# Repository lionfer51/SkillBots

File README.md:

# SkillBots
Repositorio oficial de SkillBots (RAS-UNFV)

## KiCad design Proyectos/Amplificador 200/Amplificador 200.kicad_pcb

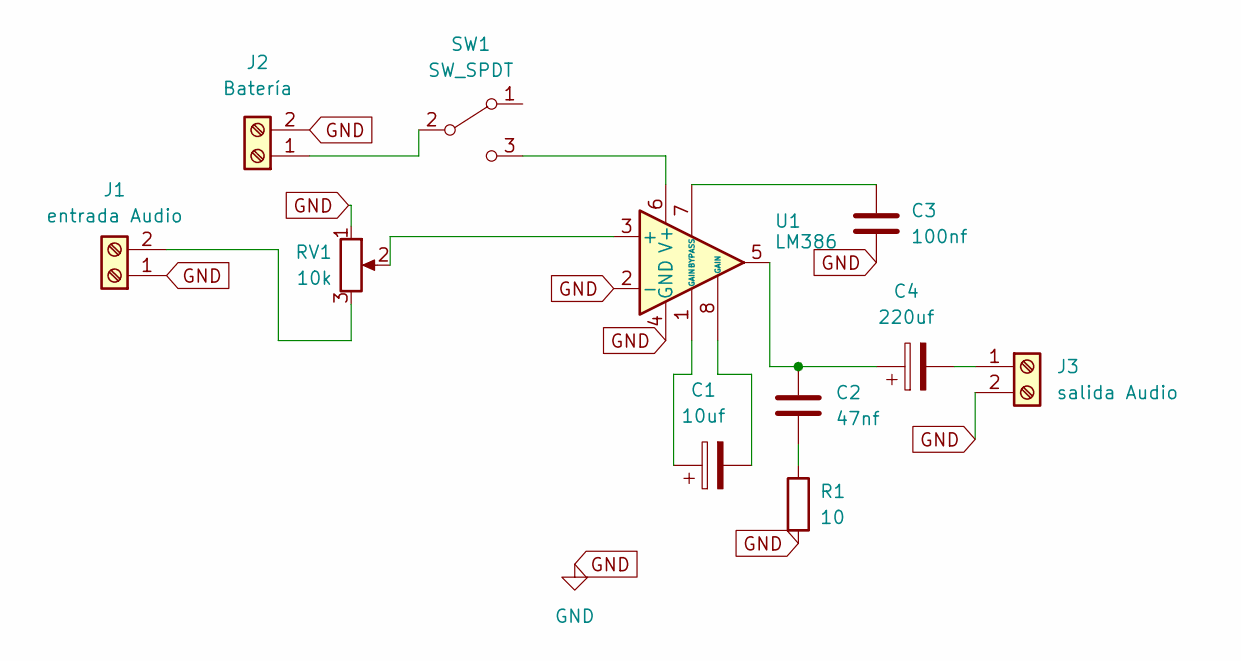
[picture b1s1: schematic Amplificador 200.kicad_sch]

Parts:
C1: 10uf; CP_Radial_D5.0mm_P2.50mm
C2: 47nf; C_Disc_D3.0mm_W2.0mm_P2.50mm
C3: 100nf; C_Disc_D3.0mm_W2.0mm_P2.50mm
C4: 220uf; CP_Radial_D5.0mm_P2.50mm
J1: entrada Audio; TerminalBlock_bornier-2_P5.08mm
J2: Batería; TerminalBlock_bornier-2_P5.08mm
J3: salida Audio; TerminalBlock_bornier-2_P5.08mm
R1: 10; R_Axial_DIN0204_L3.6mm_D1.6mm_P5.08mm_Horizontal
RV1: 10k; Potentiometer_Piher_T-16H_Single_Horizontal
SW1: SW_SPDT; SW_MINI-SPDT-SW
U1: LM386; DIP08

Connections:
GND: C3.2, J1.1, J2.2, J3.2, R1.2, RV1.1, U1.2 (-), U1.4 (GND)
unnamed: C1.1, U1.1 (GAIN)
unnamed: C1.2, U1.8 (GAIN)
unnamed: C2.1, C4.1, U1.5
unnamed: C2.2, R1.1
unnamed: J1.2, RV1.3
unnamed: J2.1, SW1.2 (B)
unnamed: C4.2, J3.1
unnamed: SW1.3 (C), U1.6 (V+)
unnamed: RV1.2, U1.3 (+)
unnamed: C3.1, U1.7 (BYPASS)

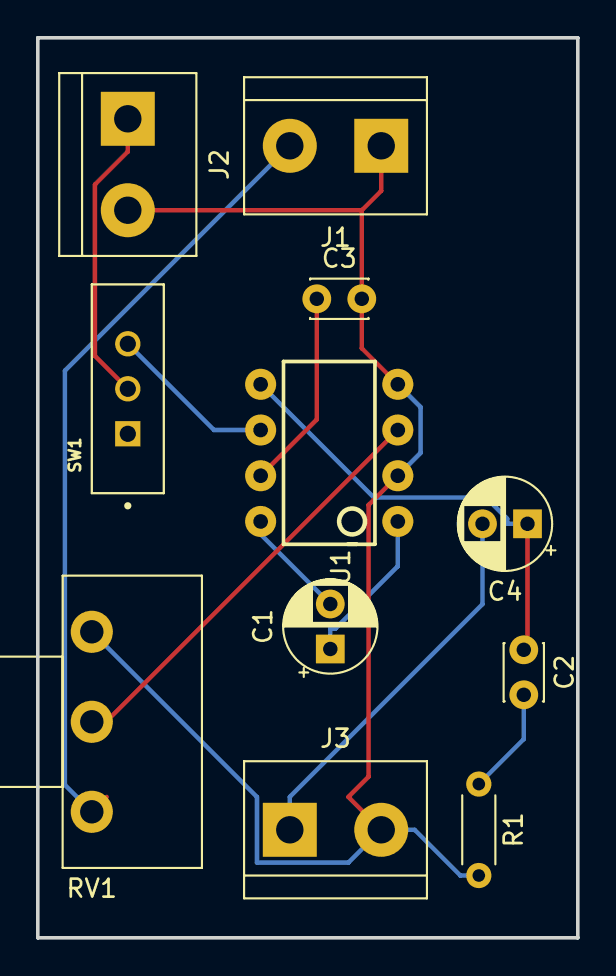
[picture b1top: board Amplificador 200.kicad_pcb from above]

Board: 2 copper layers, 30.0 x 50.0 mm, 11 parts (0 on the bottom side), 11 nets.

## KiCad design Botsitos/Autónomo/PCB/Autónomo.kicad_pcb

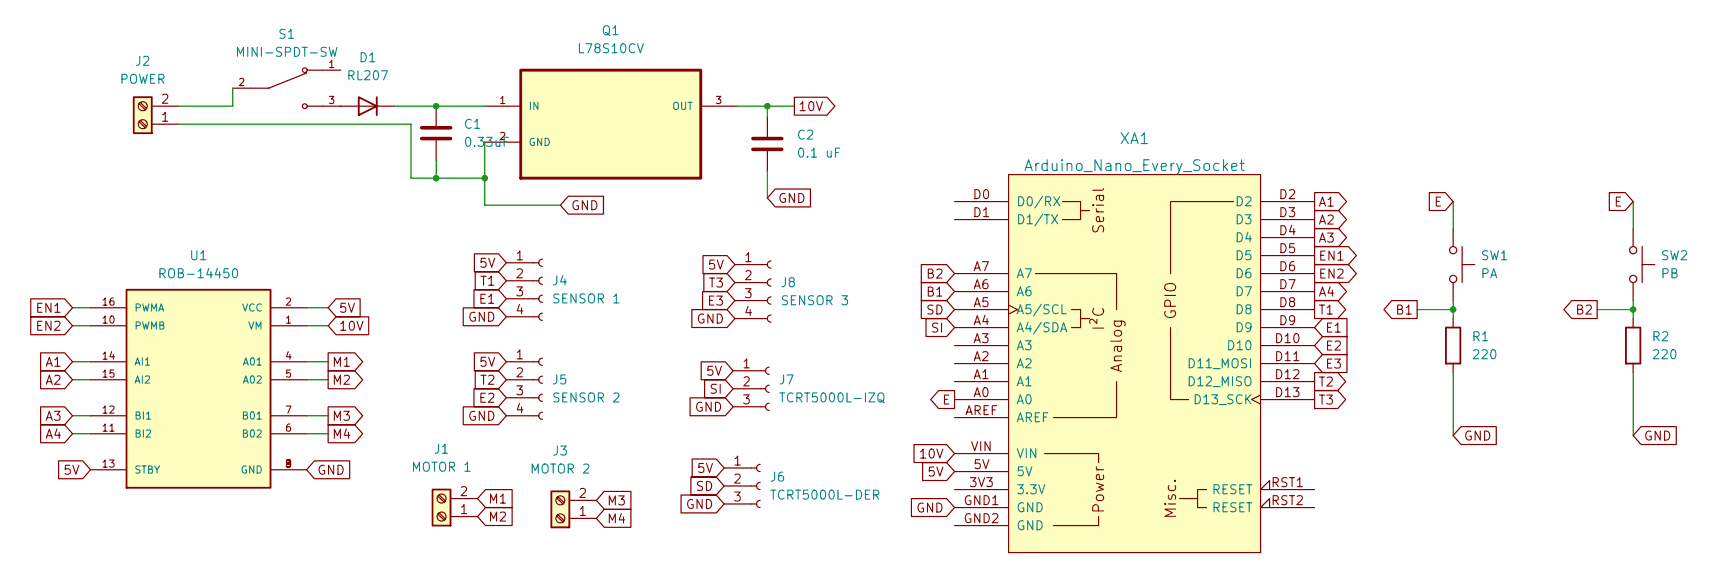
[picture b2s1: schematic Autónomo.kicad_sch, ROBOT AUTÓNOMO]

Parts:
C1: 0.33uF; C_Disc_D3.8mm_W2.6mm_P2.50mm
C2: 0.1 uF; C_Disc_D3.8mm_W2.6mm_P2.50mm
D1: RL207; D_DO-41_SOD81_P10.16mm_Horizontal
J1: MOTOR 1; TerminalBlock_bornier-2_P5.08mm
J2: POWER; TerminalBlock_bornier-2_P5.08mm
J3: MOTOR 2; TerminalBlock_bornier-2_P5.08mm
J4: SENSOR 1; PinSocket_1x04_P2.54mm_Vertical
J5: SENSOR 2; PinSocket_1x04_P2.54mm_Vertical
J6: TCRT5000L-DER; PinSocket_1x03_P2.54mm_Vertical
J7: TCRT5000L-IZQ; PinSocket_1x03_P2.54mm_Vertical
J8: SENSOR 3; PinSocket_1x04_P2.54mm_Vertical
Q1: L78S10CV; TO254P450X1020X1935-3P; MPN L78S10CV
R1, R2: 220; R_Axial_DIN0204_L3.6mm_D1.6mm_P5.08mm_Horizontal
S1: MINI-SPDT-SW; SW_MINI-SPDT-SW; PARTREV C
SW1: PA; SW_PUSH_6mm_H13mm
SW2: PB; SW_PUSH_6mm_H13mm
U1: ROB-14450; MODULE_ROB-14450; PARTREV 11-13-17
XA1: Arduino_Nano_Every_Socket

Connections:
5V: J4.1, J5.1, J6.1, J7.1, J8.1, U1.2 (VCC), U1.13 (STBY), XA1.5V
10V: C2.1, Q1.3 (OUT), U1.1 (VM), XA1.VIN
A1: U1.14 (AI1), XA1.D2
A2: U1.15 (AI2), XA1.D3
A3: U1.12 (BI1), XA1.D4
A4: U1.11 (BI2), XA1.D7
B1: R1.1, SW1.2, XA1.A6
B2: R2.1, SW2.2, XA1.A7
E: SW1.1, SW2.1, XA1.A0
E1: J4.3, XA1.D9
E2: J5.3, XA1.D10
E3: J8.3, XA1.D11 (D11_MOSI)
EN1: U1.16 (PWMA), XA1.D5
EN2: U1.10 (PWMB), XA1.D6
GND: C1.1, C2.2, J2.1, J4.4, J5.4, J6.3, J7.3, J8.4, Q1.2 (GND), R1.2, R2.2, U1.3 (GND), U1.8 (GND), U1.9 (GND), XA1.GND1 (GND)
M1: J1.2, U1.4 (A01)
M2: J1.1, U1.5 (A02)
M3: J3.2, U1.7 (B01)
M4: J3.1, U1.6 (B02)
unnamed: C1.2, D1.1 (K), Q1.1 (IN)
unnamed: D1.2 (A), S1.3
unnamed: J2.2, S1.2
SD: J6.2, XA1.A5 (A5/SCL)
SI: J7.2, XA1.A4 (A4/SDA)
T1: J4.2, XA1.D8
T2: J5.2, XA1.D12 (D12_MISO)
T3: J8.2, XA1.D13 (D13_SCK)

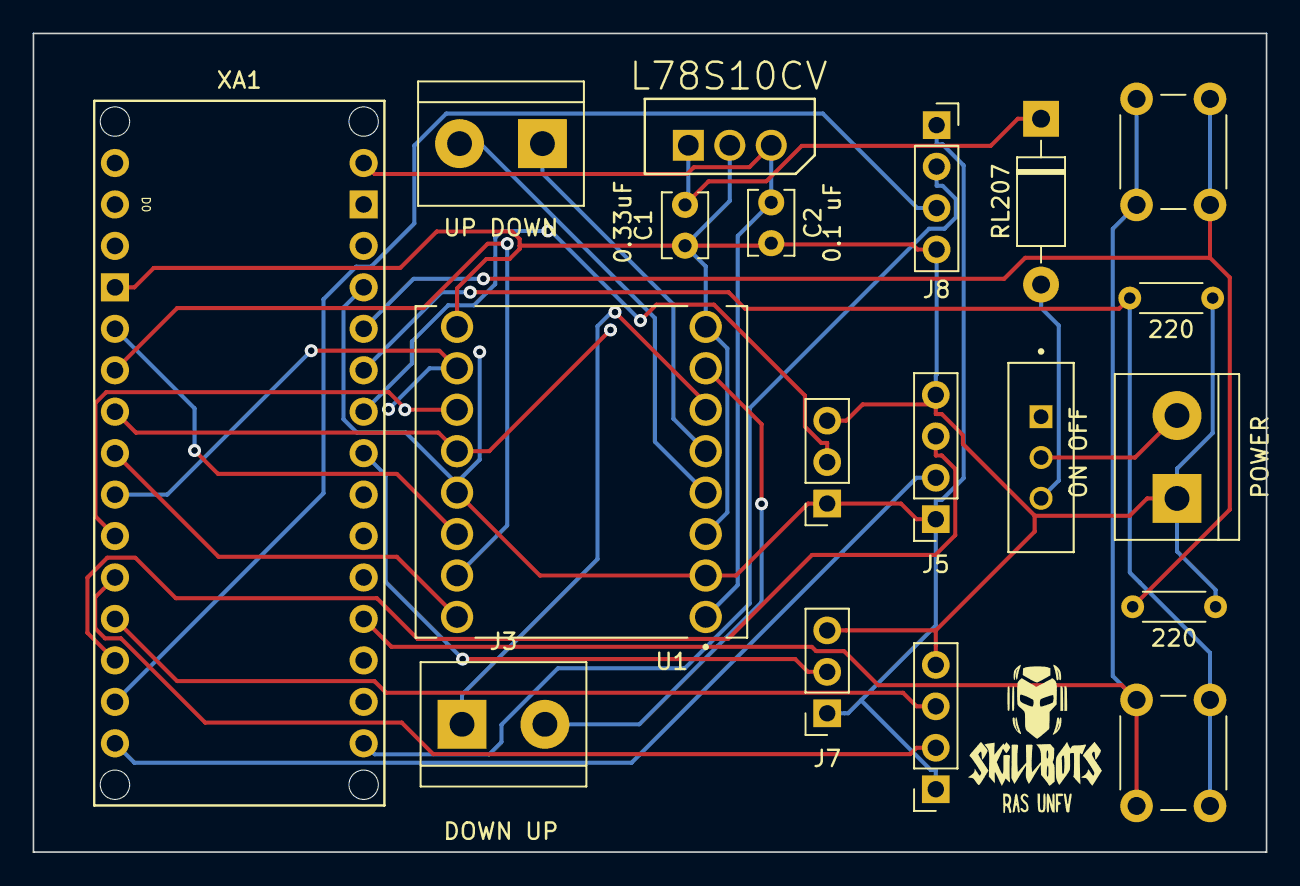
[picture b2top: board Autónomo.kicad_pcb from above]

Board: 2 copper layers, 75.6 x 50.2 mm, 19 parts (0 on the bottom side), 27 nets.

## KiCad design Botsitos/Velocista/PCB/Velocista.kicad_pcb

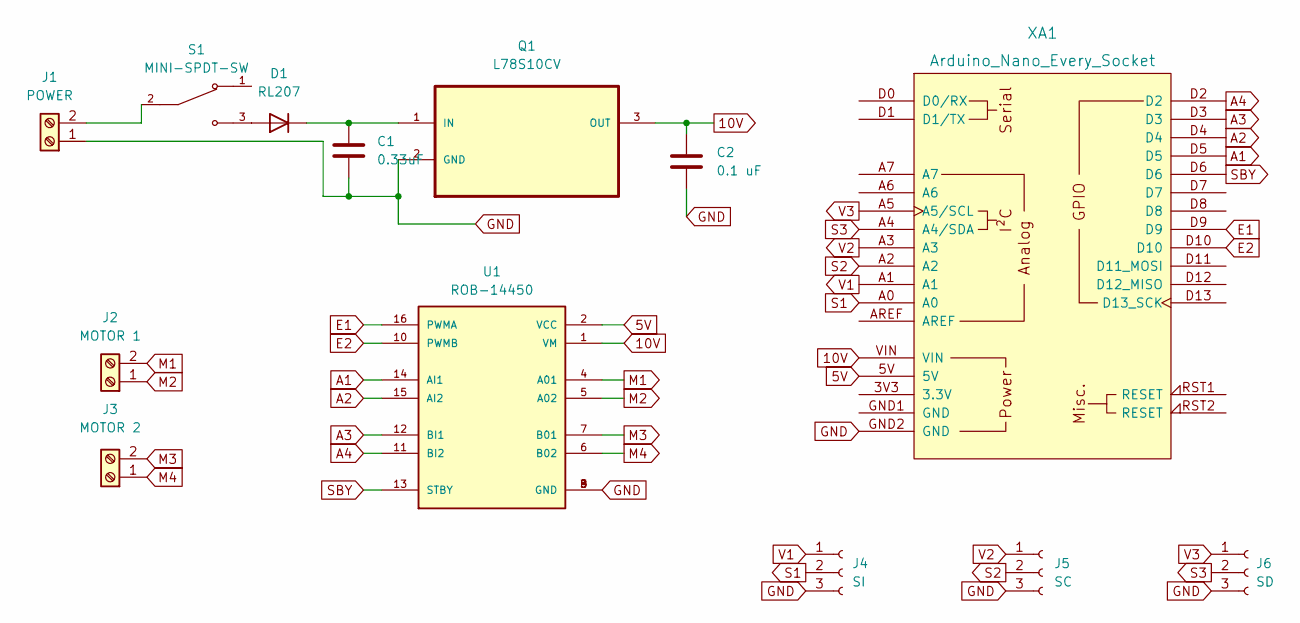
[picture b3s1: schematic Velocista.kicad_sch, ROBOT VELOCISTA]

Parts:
C1: 0.33uF; C_Disc_D3.8mm_W2.6mm_P2.50mm
C2: 0.1 uF; C_Disc_D3.8mm_W2.6mm_P2.50mm
D1: RL207; D_DO-41_SOD81_P10.16mm_Horizontal
J1: POWER; TerminalBlock_bornier-2_P5.08mm
J2: MOTOR 1; TerminalBlock_Phoenix_MPT-0,5-2-2.54_1x02_P2.54mm_Horizontal
J3: MOTOR 2; TerminalBlock_Phoenix_MPT-0,5-2-2.54_1x02_P2.54mm_Horizontal
J4: SI; PinSocket_1x03_P2.54mm_Vertical
J5: SC; PinSocket_1x03_P2.54mm_Vertical
J6: SD; PinSocket_1x03_P2.54mm_Vertical
Q1: L78S10CV; TO254P450X1020X1935-3P; MPN L78S10CV
S1: MINI-SPDT-SW; SW_MINI-SPDT-SW; PARTREV C
U1: ROB-14450; MODULE_ROB-14450; PARTREV 11-13-17
XA1: Arduino_Nano_Every_Socket

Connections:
5V: U1.2 (VCC), XA1.5V
10V: C2.1, Q1.3 (OUT), U1.1 (VM), XA1.VIN
A1: U1.14 (AI1), XA1.D5
A2: U1.15 (AI2), XA1.D4
A3: U1.12 (BI1), XA1.D3
A4: U1.11 (BI2), XA1.D2
E1: U1.16 (PWMA), XA1.D9
E2: U1.10 (PWMB), XA1.D10
GND: C1.1, C2.2, J1.1, J4.3, J5.3, J6.3, Q1.2 (GND), U1.3 (GND), U1.8 (GND), U1.9 (GND), XA1.GND2 (GND)
M1: J2.2, U1.4 (A01)
M2: J2.1, U1.5 (A02)
M3: J3.2, U1.7 (B01)
M4: J3.1, U1.6 (B02)
unnamed: C1.2, D1.1 (K), Q1.1 (IN)
unnamed: D1.2 (A), S1.3
unnamed: J1.2, S1.2
S1: J4.2, XA1.A0
S2: J5.2, XA1.A2
S3: J6.2, XA1.A4 (A4/SDA)
SBY: U1.13 (STBY), XA1.D6
V1: J4.1, XA1.A1
V2: J5.1, XA1.A3
V3: J6.1, XA1.A5 (A5/SCL)

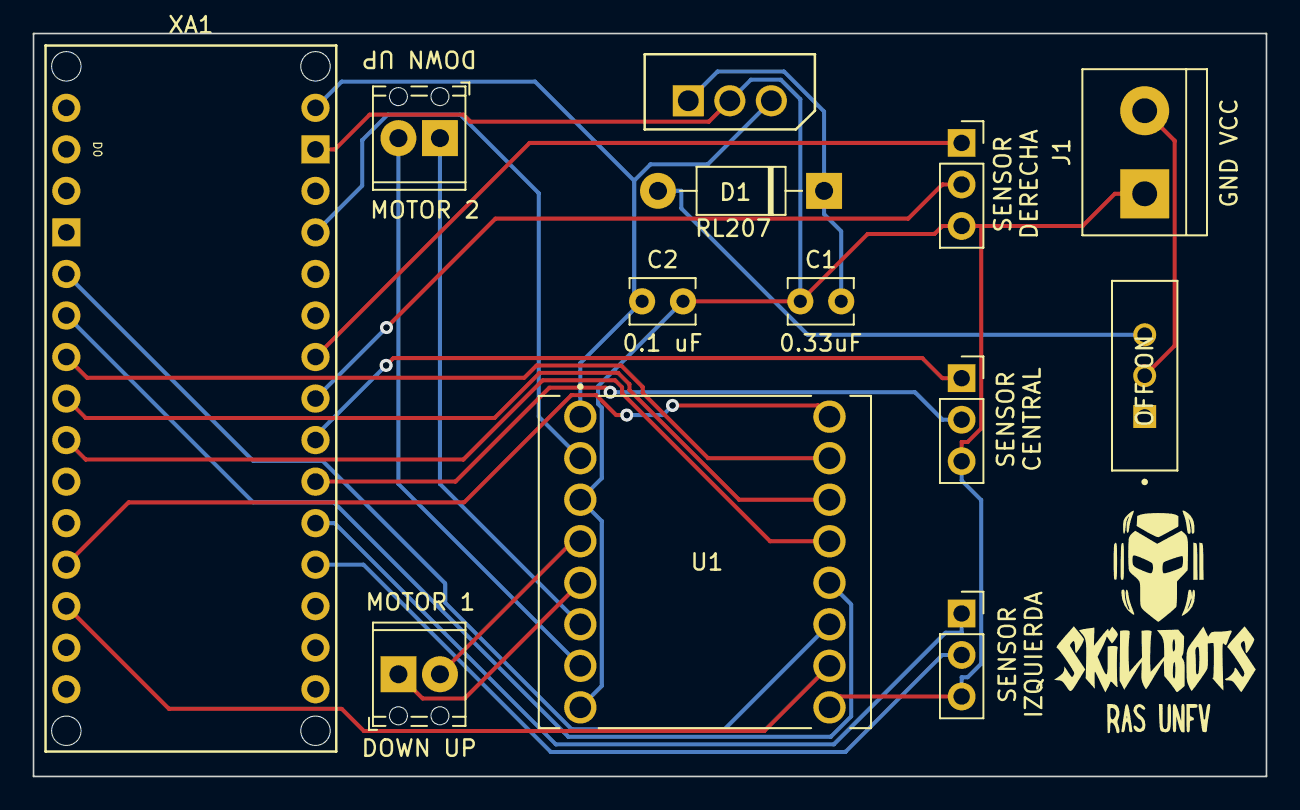
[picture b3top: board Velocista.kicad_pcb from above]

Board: 2 copper layers, 75.4 x 45.4 mm, 13 parts (0 on the bottom side), 23 nets.

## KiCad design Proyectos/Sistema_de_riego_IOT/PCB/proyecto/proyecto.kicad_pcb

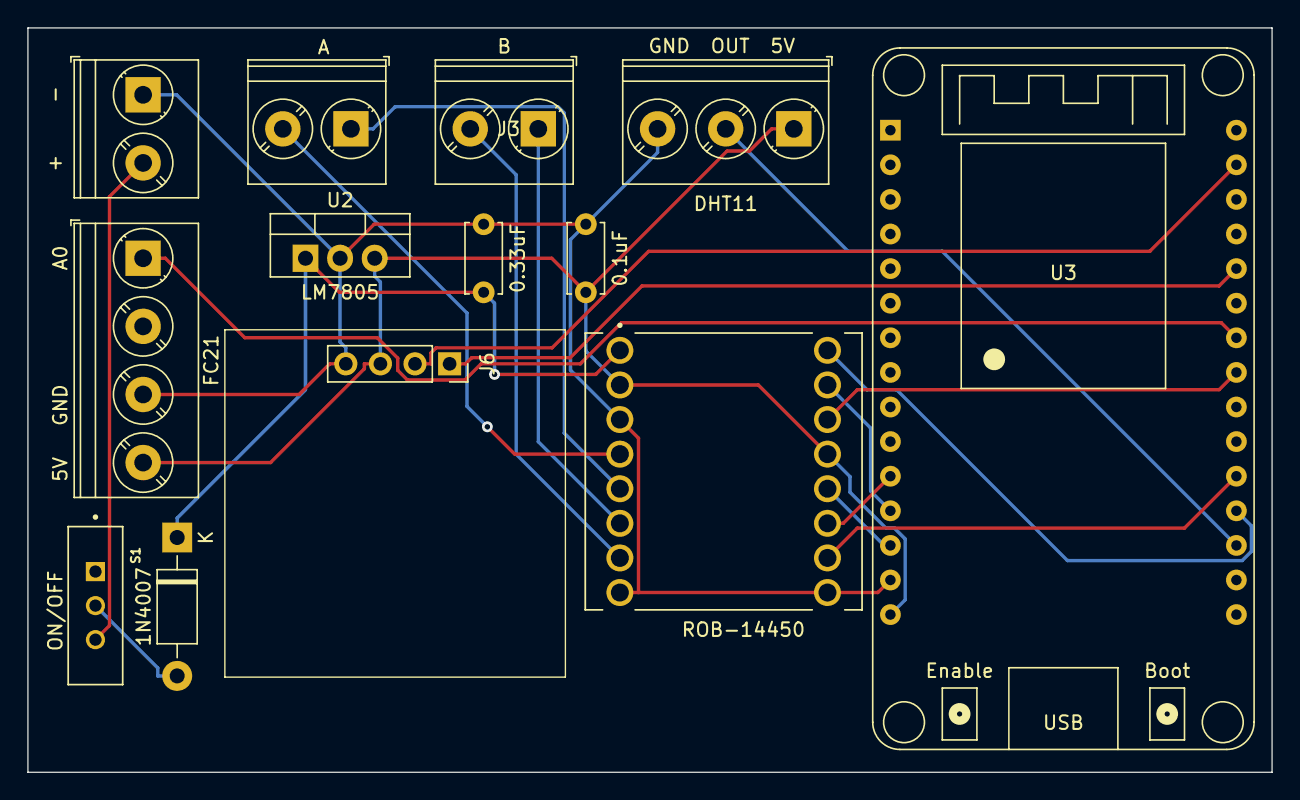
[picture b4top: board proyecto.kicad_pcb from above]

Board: 2 copper layers, 91.3 x 54.6 mm, 13 parts (0 on the bottom side), 19 nets.

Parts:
C1: 0.33uF; C_Disc_D5.0mm_W2.5mm_P5.00mm
C2: 0.1uF; C_Disc_D5.0mm_W2.5mm_P5.00mm
D1: 1N4007; D_DO-41_SOD81_P10.16mm_Horizontal
J1: + -; TerminalBlock_Phoenix_PT-1,5-2-5.0-H_1x02_P5.00mm_Horizontal
J2: DHT11; TerminalBlock_Phoenix_PT-1,5-3-5.0-H_1x03_P5.00mm_Horizontal
J3: B; TerminalBlock_Phoenix_PT-1,5-2-5.0-H_1x02_P5.00mm_Horizontal
J4: FC21; TerminalBlock_Phoenix_PT-1,5-4-5.0-H_1x04_P5.00mm_Horizontal
J5: A; TerminalBlock_Phoenix_PT-1,5-2-5.0-H_1x02_P5.00mm_Horizontal
J6: OLED; PinSocket_1x04_P2.54mm_Vertical
S1: ON/OFF; SW_MINI-SPDT-SW
U1: ROB-14450; MODULE_ROB-14450
U2: LM7805; TO-220-3_Vertical
U3: ESP32_DevKit_V1_DOIT; esp32_devkit_v1_doit

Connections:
5V: C2.1, J2.1, J4.4, J6.3, U1.2 (VCC), U1.13 (STBY), U2.3 (VO), U3.15 (VIN)
A0: J4.1, U3.24 (IO18)
GND: C1.2, C2.2, J1.1, J2.3, J4.3, J6.4, U1.3 (GND), U1.8 (GND), U1.9 (GND), U2.2 (GND), U3.14 (GND)
IA1: U1.14 (AI1), U3.23 (IO5)
IA2: U1.15 (AI2), U3.12 (IO12)
IB1: U1.12 (BI1), U3.13 (IO13)
IB2: U1.11 (BI2), U3.11 (IO14)
MA1: J5.2, U1.4 (A01)
MA2: J5.1, U1.5 (A02)
MB1: J3.2, U1.7 (B01)
MB2: J3.1, U1.6 (B02)
unnamed: D1.2 (A), S1.2
unnamed: J1.2, S1.3
OUT: J2.2, U3.18 (IO15)
PWMA: U1.16 (PWMA), U3.19 (IO2)
PWMB: U1.10 (PWMB), U3.20 (IO4)
SCL: J6.2, U3.29 (IO22)
SDA: J6.1, U3.26 (IO21)
V: C1.1, D1.1 (K), U1.1 (VM), U2.1 (VI)

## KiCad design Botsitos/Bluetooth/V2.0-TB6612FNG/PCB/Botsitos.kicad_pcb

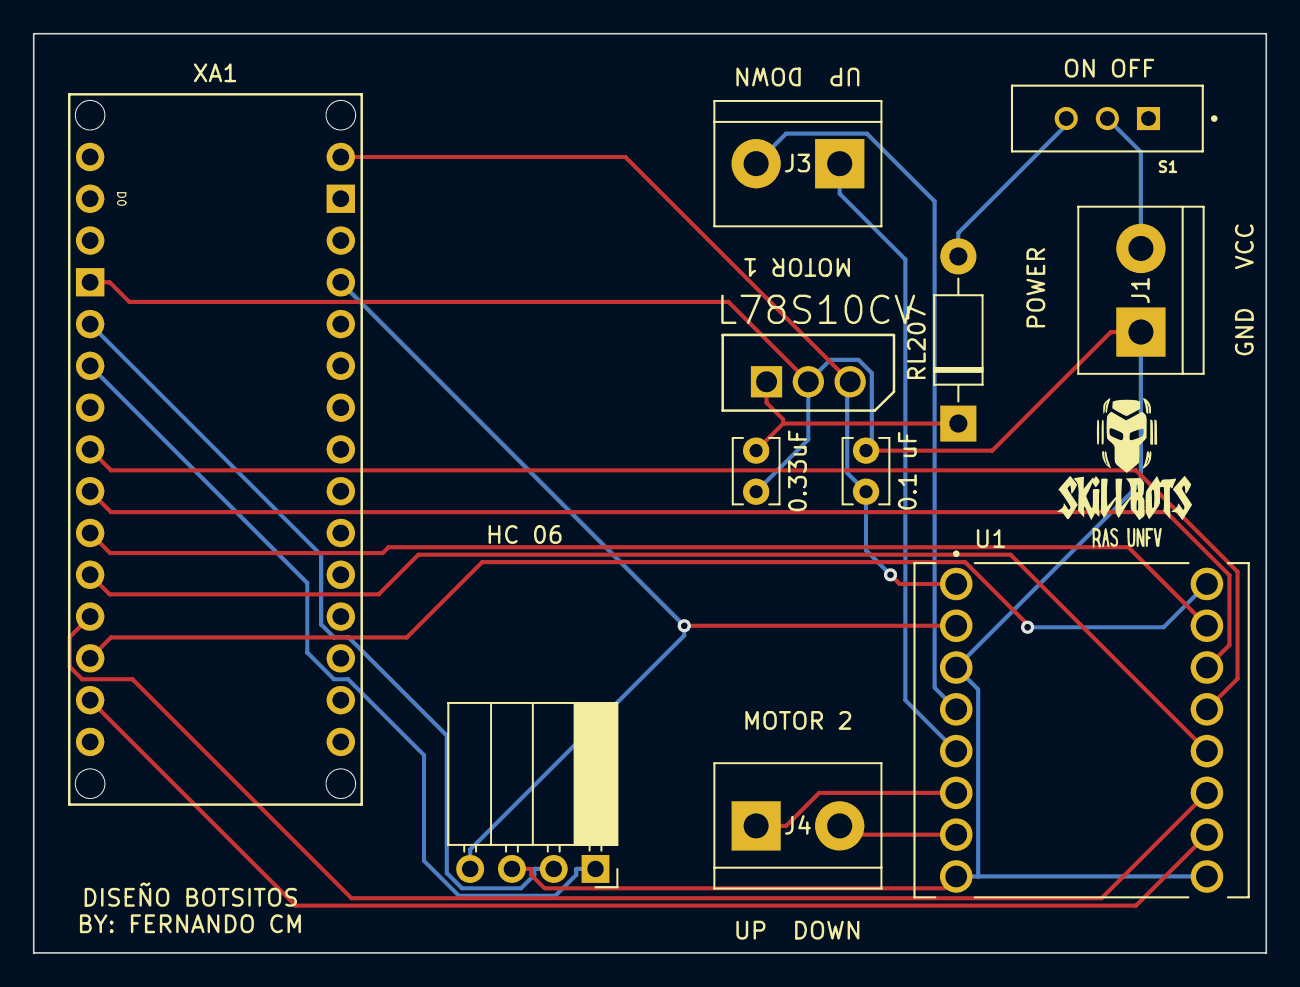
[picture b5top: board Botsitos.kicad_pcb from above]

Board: 2 copper layers, 74.9 x 55.9 mm, 11 parts (0 on the bottom side), 19 nets.

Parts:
C1: 0.33uF; C_Disc_D3.8mm_W2.6mm_P2.50mm
C2: 0.1 uF; C_Disc_D3.8mm_W2.6mm_P2.50mm
D1: RL207; D_DO-41_SOD81_P10.16mm_Horizontal
J1: POWER; TerminalBlock_bornier-2_P5.08mm
J2: HC06; PinSocket_1x04_P2.54mm_Horizontal
J3: MOTOR A; TerminalBlock_bornier-2_P5.08mm
J4: MOTOR B; TerminalBlock_bornier-2_P5.08mm
Q1: L78S10CV; TO254P450X1020X1935-3P
S1: MINI-SPDT-SW; SW_MINI-SPDT-SW
U1: ROB-14450; MODULE_ROB-14450
XA1: Arduino_Nano_Every_Socket

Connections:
5V: J2.4, U1.2 (VCC), XA1.5V
10V: C2.1, Q1.3 (OUT), U1.1 (VM), XA1.VIN
A1: U1.14 (AI1), XA1.D6
A2: U1.15 (AI2), XA1.D7
A3: U1.12 (BI1), XA1.D8
A4: U1.11 (BI2), XA1.D9
E1: U1.16 (PWMA), XA1.D10
E2: U1.10 (PWMB), XA1.D11 (D11_MOSI)
GND: C1.1, C2.2, J1.1, J2.3, Q1.2 (GND), U1.3 (GND), U1.8 (GND), U1.9 (GND), XA1.GND1 (GND)
M1: J3.2, U1.4 (A01)
M2: J3.1, U1.5 (A02)
M3: J4.2, U1.7 (B01)
M4: J4.1, U1.6 (B02)
unnamed: C1.2, D1.1 (K), Q1.1 (IN)
unnamed: D1.2 (A), S1.3
unnamed: J1.2, S1.2
RX: J2.1, XA1.D3
SBY: U1.13 (STBY), XA1.D5
TX: J2.2, XA1.D2

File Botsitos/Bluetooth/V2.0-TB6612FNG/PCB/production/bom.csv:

Designator,Footprint,Quantity,Value,LCSC Part #
C1,C_Disc_D3.8mm_W2.6mm_P2.50mm,1,0.33uF,
C2,C_Disc_D3.8mm_W2.6mm_P2.50mm,1,0.1 uF,
D1,D_DO-41_SOD81_P10.16mm_Horizontal,1,RL207,
J1,TerminalBlock_bornier-2_P5.08mm,1,POWER,
J2,PinSocket_1x04_P2.54mm_Horizontal,1,HC06,
J3,TerminalBlock_bornier-2_P5.08mm,1,MOTOR A,
J4,TerminalBlock_bornier-2_P5.08mm,1,MOTOR B,
Q1,TO254P450X1020X1935-3P,1,L78S10CV,L78S10CV
S1,SW_MINI-SPDT-SW,1,MINI-SPDT-SW,
U1,MODULE_ROB-14450,1,ROB-14450,
XA1,Arduino_Nano_Every_Socket,1,Arduino_Nano_Every_Socket,

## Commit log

2023-09-19 Agregando archivos (primer commit)
2023-09-19 Agregando
2023-09-19 SkillBots
